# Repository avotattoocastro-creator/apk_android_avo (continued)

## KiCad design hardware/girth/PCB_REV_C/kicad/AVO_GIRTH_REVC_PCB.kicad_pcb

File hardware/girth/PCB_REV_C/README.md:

# AVO GIRTH · PCB de la cincha REV C (ECG) — 15/11/2026

PCB propia y compacta de la cincha, como la del casco V5: sustituye al XIAO ESP32-C6, al módulo GY-BNO08X y al
módulo CJMCU-30003 por los mismos chips soldados en una sola placa.

**Estado:** ver `out/AVO_GIRTH_REVC_PCB_REPORTE.md` (puerta superada) o `out/AVO_GIRTH_REVC_PCB_DIAGNOSTICO_REPORTE.md`.
**No fabricada. No verificada en hardware.**

## Placa
- **40 × 26 mm**, esquinas R2, 4 capas, **1,0 mm**, ENIG. 4 taladros Ø2,2 (tornillos M2 a la tapa) en (±17,8, ±10,8).
- **Todos los componentes en la cara F** (hacia la tapa, altura máx. 2,6 mm). La cara B apoya sobre la batería.
- In1 = GND macizo · F, In2 y B = señales · rellenos GND en F y B, +3V3 en In2.
- Arquitectura y GPIO: `DOCS/INFORME_PCB_REV_C.md`.

## Bloques
- **ESP32-C6-MINI-1U-N4** (13,2 × 12,5), antena FPC en el U.FL hacia el canto +X. Mismos GPIO que el XIAO: el
  firmware **AVO GIRTH 0.5.0** funciona sin cambios.
- **BNO085** soldado, por I²C (0x4A), cristal de 32,768 kHz, en el centro de la placa.
- **MAX30003** con 1,8 V propio (RT9080-18), oscilador MEMS SiT1533 en FCLK, filtros de entrada en los electrodos.
- **Cargador BQ24072** (247 mA para la LP403048 de 500 mAh), PTC en la batería y en el contacto de 5 V, 3,3 V RT9080-33.
- **Pogos por hilos** (pads pasantes): carga P1 5V · P2 GND · P3 DET; electrodos P4 ECG + · P5 REF · P6 ECG −;
  batería J2 + · J6 −.
- **Programación:** pads TP4 (D−), TP5 (D+), TP8 (5 V), TP3 (GND), TP2 (BOOT), TP1 (EN): USB nativo del C6 con una
  pinza de pogo-pins, la primera vez. Después, por radio.

## Fuente
`fuente/avo_girth_revc_pcb.py` (piezas y redes) → `fuente/place_revc.py` (colocación) → `fuente/build.py` (placa de
colocación + esquema) → CI `build-girth-pcb-revc.yml` (Freerouting, DRC/ERC, puerta, ficheros JLCPCB). Las huellas del
MAX30003 y del SiT1533 salen de EasyEDA/LCSC (`easyeda-fp-girth-revc.yml`); la del BNO085 coincide con la de EasyEDA.

## Pendiente antes de pedir
- **MAX30003CTI+** y **BNO085** sin existencias en JLCPCB el 15/11/2026: Global Sourcing o piezas enviadas.
- Código JLCPCB del ESP32-C6-MINI-1U-N4 (el C7558096 de la REV A sale sin existencias): ver `out_stock`.
- Cápsula REV 6 (más pequeña) en FreeCAD alrededor de esta placa y de la LP403048.

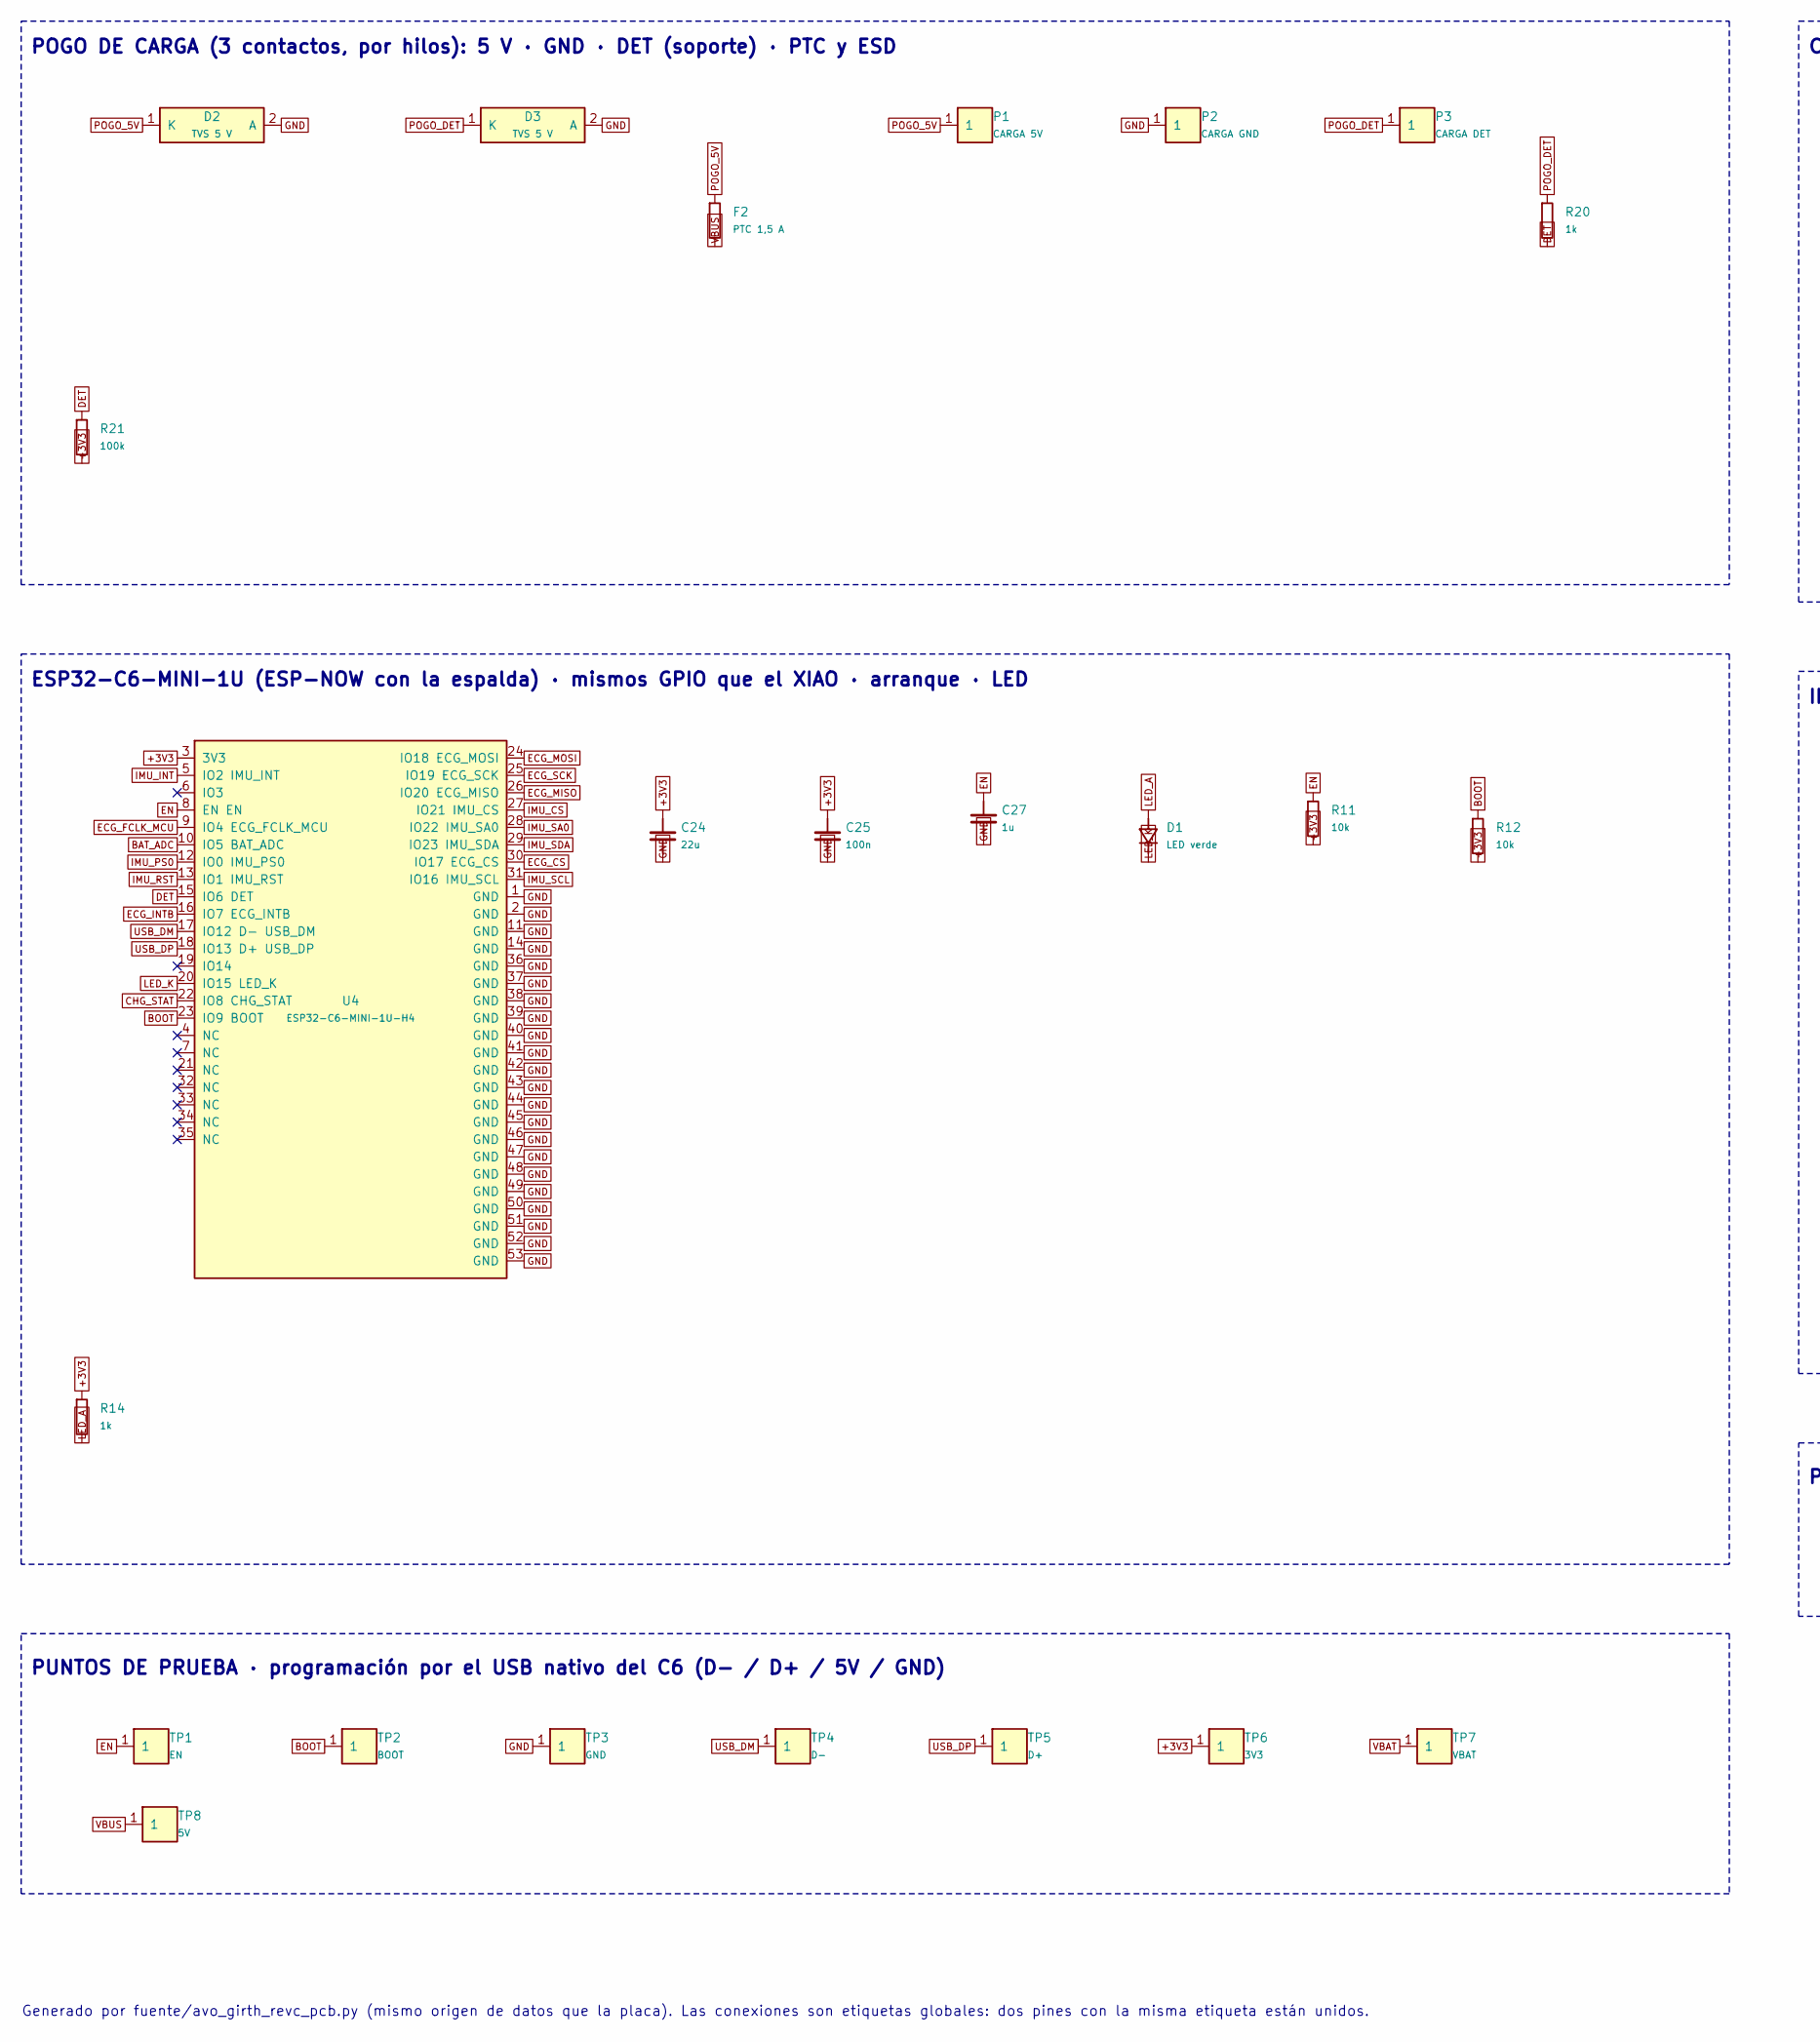
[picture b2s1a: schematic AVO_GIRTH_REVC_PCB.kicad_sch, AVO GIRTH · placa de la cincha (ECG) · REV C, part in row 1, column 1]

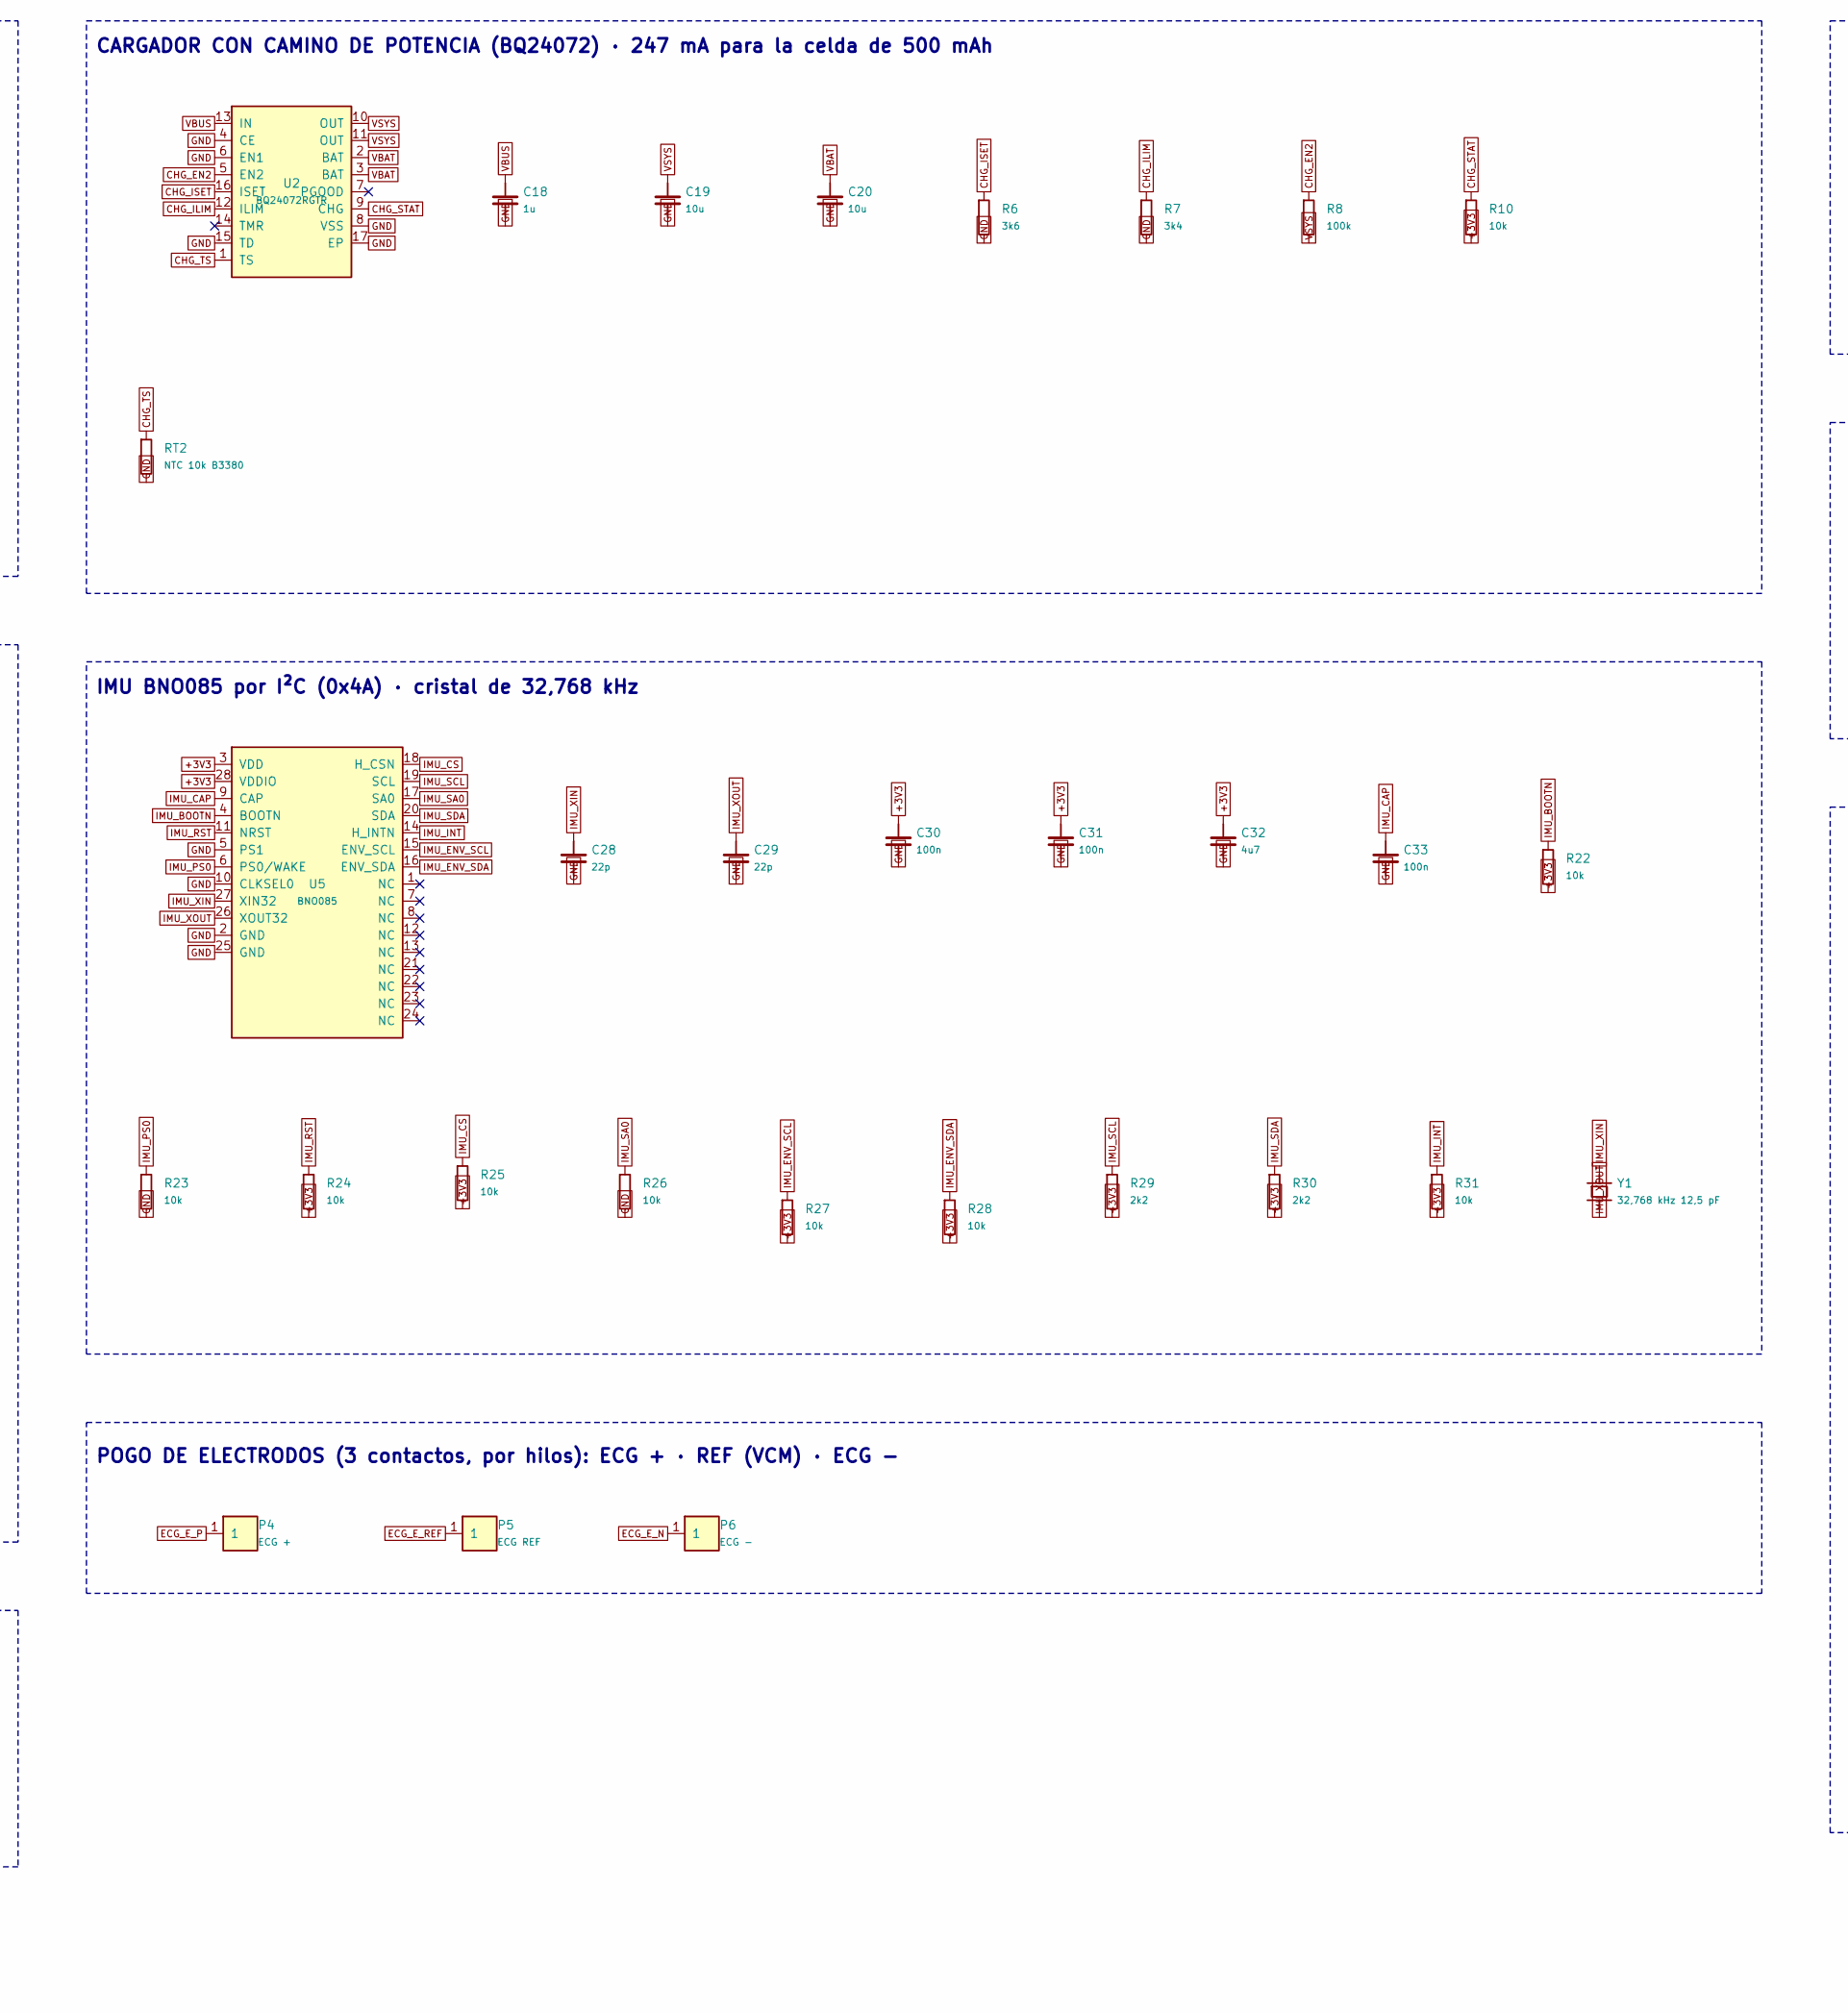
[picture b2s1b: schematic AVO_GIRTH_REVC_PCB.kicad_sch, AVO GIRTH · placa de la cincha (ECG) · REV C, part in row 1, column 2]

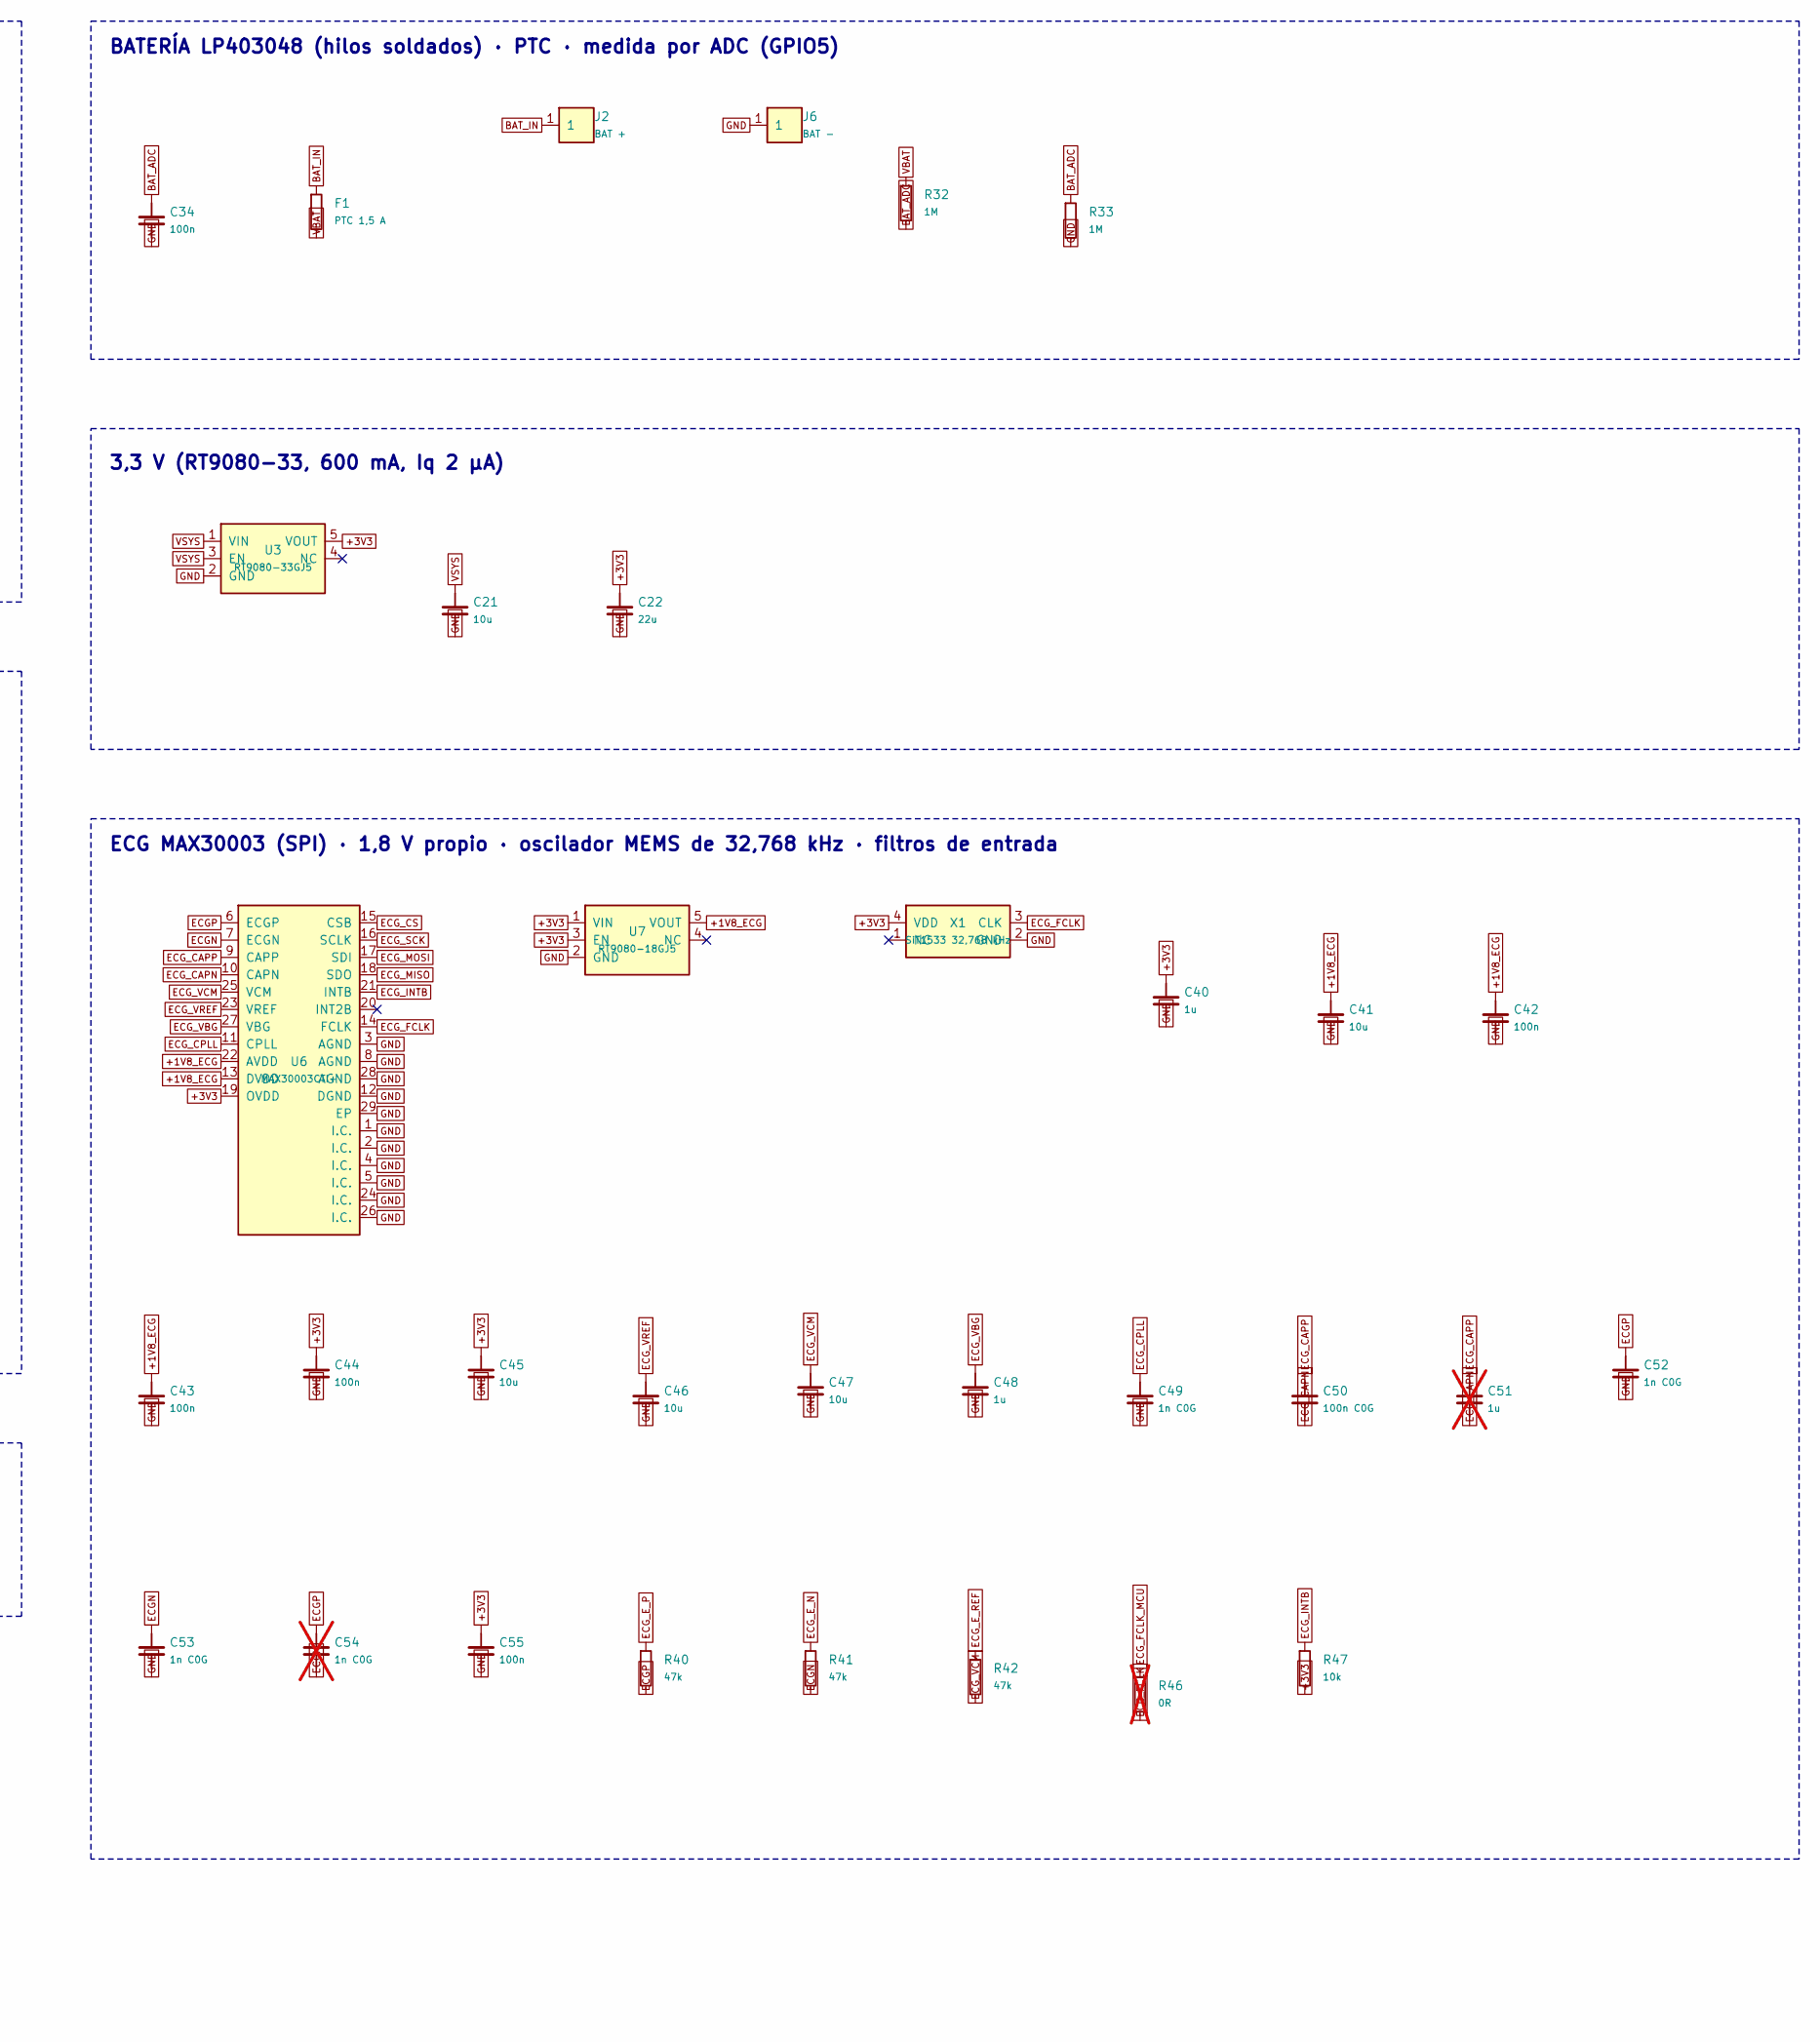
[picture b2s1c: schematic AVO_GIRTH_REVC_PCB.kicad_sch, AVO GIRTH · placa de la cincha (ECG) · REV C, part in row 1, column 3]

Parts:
C18, C27, C40, C48: 1u; C_0402_1005Metric; LCSC C52923
C19, C20, C21, C41, C45, C46, C47: 10u; C_0603_1608Metric; LCSC C96446
C22, C24: 22u; C_0805_2012Metric; LCSC C45783
C25, C30, C31, C33, C34, C42, C43, C44, C55: 100n; C_0402_1005Metric; LCSC C1525
C28, C29: 22p; C_0402_1005Metric; LCSC C1555
C32: 4u7; C_0603_1608Metric; LCSC C19666
C49, C52, C53: 1n C0G; C_0402_1005Metric; LCSC C53547
C50: 100n C0G; C_1206_3216Metric; LCSC C97946
C51: 1u; C_0402_1005Metric; LCSC C52923; not fitted
C54: 1n C0G; C_0402_1005Metric; LCSC C53547; not fitted
D1: LED verde; LED_0603_1608Metric; LCSC C2286
D2, D3: TVS 5 V; D_SOD-323; MPN PESD5V0S1BA; LCSC C2827694
F1, F2: PTC 1,5 A; Fuse_1206_3216Metric; MPN SMD1206P150TF; LCSC C20802
J2: BAT +; WirePad_D1.5_Drill0.8
J6: BAT -; WirePad_D1.5_Drill0.8
P1: CARGA 5V; WirePad_D1.5_Drill0.8
P2: CARGA GND; WirePad_D1.5_Drill0.8
P3: CARGA DET; WirePad_D1.5_Drill0.8
P4: ECG +; WirePad_D1.5_Drill0.8
P5: ECG REF; WirePad_D1.5_Drill0.8
P6: ECG -; WirePad_D1.5_Drill0.8
R6: 3k6; R_0402_1005Metric; LCSC C25891
R7: 3k4; R_0402_1005Metric; LCSC C4940
R8, R21: 100k; R_0402_1005Metric; LCSC C25741
R10, R11, R12, R22, R23, R24, R25, R26, R27, R28, R31, R47: 10k; R_0402_1005Metric; LCSC C25744
R14, R20: 1k; R_0402_1005Metric; LCSC C11702
R29, R30: 2k2; R_0402_1005Metric; LCSC C25879
R32, R33: 1M; R_0402_1005Metric; LCSC C26083
R40, R41, R42: 47k; R_0402_1005Metric; LCSC C25792
R46: 0R; R_0402_1005Metric; LCSC C17168; not fitted
RT2: NTC 10k B3380; R_0402_1005Metric; MPN NCP15XH103F03RC; LCSC C77131
TP1: EN; TestPoint_Pad_D1.0mm
TP2: BOOT; TestPoint_Pad_D1.0mm
TP3: GND; TestPoint_Pad_D1.0mm
TP4: D-; TestPoint_Pad_D1.0mm
TP5: D+; TestPoint_Pad_D1.0mm
TP6: 3V3; TestPoint_Pad_D1.0mm
TP7: VBAT; TestPoint_Pad_D1.0mm
TP8: 5V; TestPoint_Pad_D1.0mm
U2: BQ24072RGTR; VQFN-16-1EP_3x3mm_P0.5mm_EP1.68x1.68mm_ThermalVias; MPN BQ24072RGTR; LCSC C140288
U3: RT9080-33GJ5; SOT-23-5; MPN RT9080-33GJ5; LCSC C841192
U4: ESP32-C6-MINI-1U-H4; ESP32-C6-MINI-1U; MPN ESP32-C6-MINI-1U-H4 (alt. -N4); LCSC C20627095
U5: BNO085; CEVA_BNO08x_LGA-28_5.2x3.8mm_P0.5mm; MPN BNO085 (alt. BNO086); LCSC C5189642
U6: MAX30003CTI+; AVO_TQFN-28-1EP_5x5mm_P0.5mm_EP3.35mm; MPN MAX30003CTI+ (Analog Devices); LCSC C1519515
U7: RT9080-18GJ5; SOT-23-5; MPN RT9080-18GJ5; LCSC C426476
X1: SiT1533 32,768 kHz; AVO_SiT1533_2.0x1.2mm; MPN SIT1533AI-H4-DCC-32.768E (SiTime); LCSC C367058
Y1: 32,768 kHz 12,5 pF; Crystal_SMD_3215-2Pin_3.2x1.5mm; MPN Q13FC13500004; LCSC C32346

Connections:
+1V8_ECG: C41.1, C42.1, C43.1, U6.13 (DVDD), U6.22 (AVDD), U7.5 (VOUT)
+3V3: C22.1, C24.1, C25.1, C30.1, C31.1, C32.1, C40.1, C44.1, C45.1, C55.1, R10.2, R11.2, R12.2, R14.1, R21.2, R22.2, R24.2, R25.2, R27.2, R28.2, R29.2, R30.2, R31.2, R47.2, TP6.1, U3.5 (VOUT), U4.3 (3V3), U5.3 (VDD), U5.28 (VDDIO), U6.19 (OVDD), U7.1 (VIN), U7.3 (EN), X1.4 (VDD)
BAT_ADC: C34.1, R32.2, R33.1, U4.10 (IO5 BAT_ADC)
BAT_IN: F1.1, J2.1
BOOT: R12.1, TP2.1, U4.23 (IO9 BOOT)
CHG_EN2: R8.1, U2.5 (EN2)
CHG_ILIM: R7.1, U2.12 (ILIM)
CHG_ISET: R6.1, U2.16 (ISET)
CHG_STAT: R10.1, U2.9 (CHG), U4.22 (IO8 CHG_STAT)
CHG_TS: RT2.1, U2.1 (TS)
DET: R20.2, R21.1, U4.15 (IO6 DET)
ECGN: C53.1, C54.2, R41.2, U6.7 (ECGN)
ECGP: C52.1, C54.1, R40.2, U6.6 (ECGP)
ECG_CAPN: C50.2, C51.2, U6.10 (CAPN)
ECG_CAPP: C50.1, C51.1, U6.9 (CAPP)
ECG_CPLL: C49.1, U6.11 (CPLL)
ECG_CS: U4.30 (IO17 ECG_CS), U6.15 (CSB)
ECG_E_N: P6.1, R41.1
ECG_E_P: P4.1, R40.1
ECG_E_REF: P5.1, R42.1
ECG_FCLK: R46.2, U6.14 (FCLK), X1.3 (CLK)
ECG_FCLK_MCU: R46.1, U4.9 (IO4 ECG_FCLK_MCU)
ECG_INTB: R47.1, U4.16 (IO7 ECG_INTB), U6.21 (INTB)
ECG_MISO: U4.26 (IO20 ECG_MISO), U6.18 (SDO)
ECG_MOSI: U4.24 (IO18 ECG_MOSI), U6.17 (SDI)
ECG_SCK: U4.25 (IO19 ECG_SCK), U6.16 (SCLK)
ECG_VBG: C48.1, U6.27 (VBG)
ECG_VCM: C47.1, R42.2, U6.25 (VCM)
ECG_VREF: C46.1, U6.23 (VREF)
EN: C27.1, R11.1, TP1.1, U4.8 (EN EN)
GND: C18.2, C19.2, C20.2, C21.2, C22.2, C24.2, C25.2, C27.2, C28.2, C29.2, C30.2, C31.2, C32.2, C33.2, C34.2, C40.2, C41.2, C42.2, C43.2, C44.2, C45.2, C46.2, C47.2, C48.2, C49.2, C52.2, C53.2, C55.2, D2.2 (A), D3.2 (A), J6.1, P2.1, R6.2, R7.2, R23.2, R26.2, R33.2, RT2.2, TP3.1, U2.4 (CE), U2.6 (EN1), U2.8 (VSS), U2.15 (TD), U2.17 (EP), U3.2 (GND), U4.1 (GND), U4.2 (GND), U4.11 (GND), U4.14 (GND), U4.36 (GND), U4.37 (GND), U4.38 (GND), U4.39 (GND), U4.40 (GND), U4.41 (GND), U4.42 (GND), U4.43 (GND), U4.44 (GND), U4.45 (GND), U4.46 (GND), U4.47 (GND), U4.48 (GND), U4.49 (GND), U4.50 (GND), U4.51 (GND), U4.52 (GND), U4.53 (GND), U5.2 (GND), U5.5 (PS1), U5.10 (CLKSEL0), U5.25 (GND), U6.1 (I.C.), U6.2 (I.C.), U6.3 (AGND), U6.4 (I.C.), U6.5 (I.C.), U6.8 (AGND), U6.12 (DGND), U6.24 (I.C.), U6.26 (I.C.), U6.28 (AGND), U6.29 (EP), U7.2 (GND), X1.2 (GND)
IMU_BOOTN: R22.1, U5.4 (BOOTN)
IMU_CAP: C33.1, U5.9 (CAP)
IMU_CS: R25.1, U4.27 (IO21 IMU_CS), U5.18 (H_CSN)
IMU_ENV_SCL: R27.1, U5.15 (ENV_SCL)
IMU_ENV_SDA: R28.1, U5.16 (ENV_SDA)
IMU_INT: R31.1, U4.5 (IO2 IMU_INT), U5.14 (H_INTN)
IMU_PS0: R23.1, U4.12 (IO0 IMU_PS0), U5.6 (PS0/WAKE)
IMU_RST: R24.1, U4.13 (IO1 IMU_RST), U5.11 (NRST)
IMU_SA0: R26.1, U4.28 (IO22 IMU_SA0), U5.17 (SA0)
IMU_SCL: R29.1, U4.31 (IO16 IMU_SCL), U5.19 (SCL)
IMU_SDA: R30.1, U4.29 (IO23 IMU_SDA), U5.20 (SDA)
IMU_XIN: C28.1, U5.27 (XIN32), Y1.1
IMU_XOUT: C29.1, U5.26 (XOUT32), Y1.2
LED_A: D1.2 (A), R14.2
LED_K: D1.1 (K), U4.20 (IO15 LED_K)
POGO_5V: D2.1 (K), F2.1, P1.1
POGO_DET: D3.1 (K), P3.1, R20.1
USB_DM: TP4.1, U4.17 (IO12 D- USB_DM)
USB_DP: TP5.1, U4.18 (IO13 D+ USB_DP)
VBAT: C20.1, F1.2, R32.1, TP7.1, U2.2 (BAT), U2.3 (BAT)
VBUS: C18.1, F2.2, TP8.1, U2.13 (IN)
VSYS: C19.1, C21.1, R8.2, U2.10 (OUT), U2.11 (OUT), U3.1 (VIN), U3.3 (EN)

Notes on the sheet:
POGO DE CARGA (3 contactos, por hilos): 5 V · GND · DET (soporte) · PTC y ESD
CARGADOR CON CAMINO DE POTENCIA (BQ24072) · 247 mA para la celda de 500 mAh
3,3 V (RT9080-33, 600 mA, Iq 2 µA)
ESP32-C6-MINI-1U (ESP-NOW con la espalda) · mismos GPIO que el XIAO · arranque · LED
IMU BNO085 por I²C (0x4A) · cristal de 32,768 kHz
ECG MAX30003 (SPI) · 1,8 V propio · oscilador MEMS de 32,768 kHz · filtros de entrada
BATERÍA LP403048 (hilos soldados) · PTC · medida por ADC (GPIO5)
POGO DE ELECTRODOS (3 contactos, por hilos): ECG + · REF (VCM) · ECG −
PUNTOS DE PRUEBA · programación por el USB nativo del C6 (D− / D+ / 5V / GND)
Generado por fuente/avo_girth_revc_pcb.py (mismo origen de datos que la placa). Las conexiones son etiquetas globales: dos pines con la misma etiqueta están unidos.

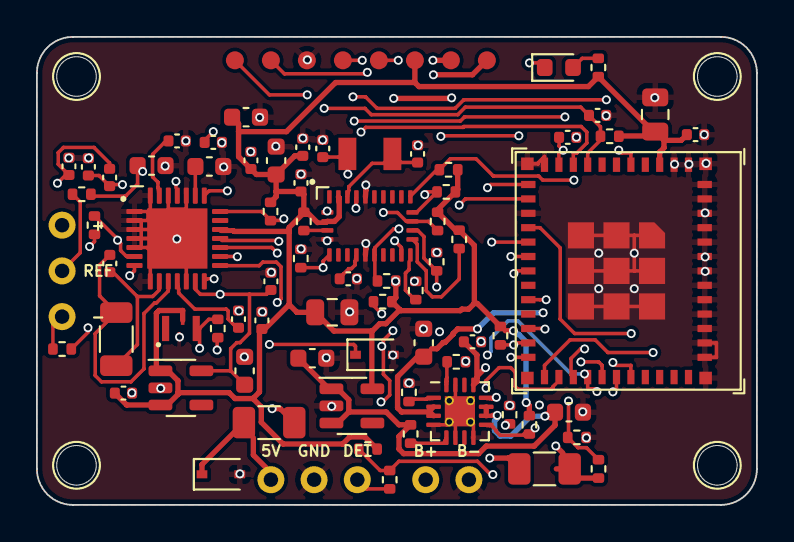
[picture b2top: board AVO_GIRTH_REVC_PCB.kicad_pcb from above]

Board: 4 copper layers, 40.0 x 26.0 mm, 91 parts (0 on the bottom side), 53 nets.

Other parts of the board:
H1, H2, H3, H4: TALADRO M2; AVO_Taladro_NPTH_D2.2

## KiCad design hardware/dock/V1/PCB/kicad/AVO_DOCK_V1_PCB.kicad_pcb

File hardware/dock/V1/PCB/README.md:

# AVO DOCK V1 · PCB REV A (15/11/2026)

**Estado:** diseño verificado por software en el CI con KiCad 9 (ejecución 43789462892):
- DRC: 0 errores y 0 conexiones incompletas;
- paridad esquema ↔ placa: 0;
- ERC: 0/0;
- puerta superada.

Los ficheros de fabricación están en `out/FINAL/`. **No fabricada. No verificada en hardware.**

**Ruteado:** Freerouting 1.9.0 de la ejecución 43788505774. Se guarda tal cual en `kicad/AVO_DOCK_V1_PCB_ruteado.kicad_pcb` y el CI lo reutiliza sin volver a rutear. Si cambia la colocación, hay que borrar ese fichero.

## Cómo se genera
```
cd fuente
python3 place_dock.py      # colocación → colocacion_dock.json y ../pcb_mecanica.json (lo lee el CAD)
python3 build.py           # placa de colocación + vías a planos, esquema, proyecto y piezas.json
```
En el CI se hace el ruteado (Freerouting 1.9.0), el relleno de zonas, el DRC con paridad y el ERC. Después viene la puerta de fabricación (`fuente/gate.py`). Solo si la supera se generan los Gerber, la BOM y el CPL de JLCPCB y el STEP en `out/FINAL/`.

## Placa
- 130 × 76 mm, esquinas R3, 4 capas, 1,6 mm, ENIG. Todos los componentes en la cara F.
- Capas: F.Cu y B.Cu de señal (con relleno GND tras el ruteado); In1 = plano GND; In2 = plano +3V3 (vía desde cada pad).
- **Zona de red** en (−65…−46, −12…38) con un **foso de 6,5 mm** sin cobre en ninguna capa. Las pistas de red (1,0 mm, F.Cu) las traza el generador.
- 4 taladros NPTH Ø3,2 para M3 de nailon.

Arquitectura, conexiones y pendientes: `../DOCS/ARQUITECTURA.md`.

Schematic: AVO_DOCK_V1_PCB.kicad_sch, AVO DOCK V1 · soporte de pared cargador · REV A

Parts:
C1, C5: 47u 6V3; C_0805_2012Metric; LCSC C16780
C2, C8, C10, C13, C14, C16, C20, C21, C22, C23, C24, C25, C27, C28, C29, C40, C41, C42, C43, C44, C45, C46, C47: 100n; C_0402_1005Metric; LCSC C1525
C3, C15, C48, C49, C50, C51: 10u 25V; C_0603_1608Metric; LCSC C96446
C4: 100u 10V; CP_EIA-3528-21_Kemet-B; MPN TAJB107K010RNJ (AVX) o equivalente
C6, C7, C9: 22u 10V; C_0805_2012Metric; LCSC C45783
C11, C12: 1u; C_0402_1005Metric; LCSC C52923
C26: 4u7; C_0603_1608Metric; LCSC C19666
C30, C31: 18p; C_0402_1005Metric; LCSC C1549
D1, D10, D11, D12, D13, D14, D15, D16, D17: TVS 5 V; D_SOD-323; MPN PESD5V0S1BA; LCSC C2827694
F1: T1A 250V; Fuse_Littelfuse_372_D8.50mm; MPN Littelfuse 37211000411 (TR5, T 1 A)
F2: PTC 1,5 A; Fuse_1206_3216Metric; MPN SMD1206P150TF; LCSC C20802
J1: RED L; WirePad_D2.6_Drill1.3
J2: RED N; WirePad_D2.6_Drill1.3
J3: USB-C PC; USB_C_Receptacle_HRO_TYPE-C-31-M-12; MPN TYPE-C-31-M-12 (HRO); LCSC C165948
J4: PANTALLA 2" ST7789; JST_GH_SM08B-GHS-TB_1x08-1MP_P1.25mm_Horizontal; MPN SM08B-GHS-TB (JST)
P1: A VBUS; WirePad_D1.7_Drill0.9
P2: A D-; WirePad_D1.7_Drill0.9
P3: A D+; WirePad_D1.7_Drill0.9
P4: A GND; WirePad_D1.7_Drill0.9
P5: A AUX; WirePad_D1.7_Drill0.9
P6: B VBUS; WirePad_D1.7_Drill0.9
P7: B D-; WirePad_D1.7_Drill0.9
P8: B D+; WirePad_D1.7_Drill0.9
P9: B GND; WirePad_D1.7_Drill0.9
P10: B AUX; WirePad_D1.7_Drill0.9
P11: GA +5V; WirePad_D1.7_Drill0.9
P12: GA GND; WirePad_D1.7_Drill0.9
P13: GA MTCK; WirePad_D1.7_Drill0.9
P14: GB +5V; WirePad_D1.7_Drill0.9
P15: GB GND; WirePad_D1.7_Drill0.9
P16: GB MTCK; WirePad_D1.7_Drill0.9
P20: PULSADOR; WirePad_D1.7_Drill0.9
P21: PULSADOR GND; WirePad_D1.7_Drill0.9
PS1: IRM-20-5; Converter_ACDC_MeanWell_IRM-20-xx_THT; MPN Mean Well IRM-20-5 (5 V 4 A)
Q1, Q1B, Q2: AO3401A; SOT-23; LCSC C15127
Q3: 2N7002; SOT-23; LCSC C8545
R1, R2, R5, R6, R8, R9, R10, R12, R13, R17, R28, R44, R45, R46, R47: 100k; R_0402_1005Metric; LCSC C25741
R3, R4: 5k1; R_0402_1005Metric; LCSC C25905
R7, R14, R21, R22, R23, R24, R26, R29, R30, R31, R32: 10k; R_0402_1005Metric; LCSC C25744
R11: 0R; R_0402_1005Metric; LCSC C17168
R15, R16, R52, R53, R54, R55: 22R; R_0402_1005Metric; LCSC C25092
R20: 12k; R_0402_1005Metric; LCSC C25752
R27: 68k; R_0402_1005Metric; LCSC C36871
R40, R41: 24k9; R_0402_1005Metric
R42, R43: 49k9; R_0402_1005Metric
R48, R49, R50, R51: 50m 1%; R_0805_2012Metric
R56, R57, R60, R61: 1k; R_0402_1005Metric; LCSC C11702
R62, R63: 47k; R_0402_1005Metric; LCSC C25792
RV1: MOV 275 VAC; RV_Disc_D7mm_W4.8mm_P5mm; MPN S07K275 (TDK) o equivalente
TP1: EN; TestPoint_Pad_D1.0mm
TP2: BOOT; TestPoint_Pad_D1.0mm
TP3: GND; TestPoint_Pad_D1.0mm
TP4: TXD0; TestPoint_Pad_D1.0mm
TP5: RXD0; TestPoint_Pad_D1.0mm
TP6: 3V3; TestPoint_Pad_D1.0mm
TP7: 5V_SYS; TestPoint_Pad_D1.0mm
TP8: 5V_RED; TestPoint_Pad_D1.0mm
TP9: VBUS_PC; TestPoint_Pad_D1.0mm
U1, U18, U19: USBLC6-2SC6; SOT-23-6; LCSC C7519
U2: AMS1117-3.3; SOT-223; MPN AMS1117-3.3; LCSC C6186
U3: ESP32-S3-MINI-1U-N8; ESP32-S3-MINI-1U; MPN ESP32-S3-MINI-1U-N8; LCSC C2980299
U4, U5: TS3USB221; DFN-10-1EP_3x3mm_P0.5mm_EP1.65x2.38mm; MPN TS3USB221ADRCR
U6: USB2514B-I/M2; QFN-36-1EP_6x6mm_P0.5mm_EP3.7x3.7mm_ThermalVias; MPN USB2514B-I/M2 (Microchip); LCSC C220679
U10, U11, U12, U13: TPS2553DBVR; SOT-23-6; MPN TPS2553DBVR (TI)
U14, U15, U16, U17: INA180A2; SOT-23-5; MPN INA180A2IDBVR (TI)
Y1: 24 MHz; Crystal_SMD_3225-4Pin_3.2x2.5mm; MPN X322524MOB4SI (Yangxing) 24 MHz 12 pF o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

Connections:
+3V3: C7.1, C8.1, C9.1, C10.1, C11.1, C13.1, C14.1, C15.1, C20.1, C21.1, C22.1, C23.1, C24.1, C25.1, C26.1, C44.1, C45.1, C46.1, C47.1, J4.2 (VCC), R14.2, R24.2, R26.2, R30.2, R31.2, R32.2, R62.2, R63.2, TP6.1, U2.2 (VOUT), U2.4 (TAB), U3.3 (3V3), U4.10 (VCC), U5.10 (VCC), U6.5 (VDDA33), U6.8 (DN4_DM/PRT_DIS_M4), U6.9 (DN4_DP/PRT_DIS_P4), U6.10 (VDDA33), U6.13 (OCS_N1), U6.15 (VDD33), U6.17 (OCS_N2), U6.19 (OCS_N3), U6.21 (OCS_N4), U6.23 (VDD33), U6.29 (VDDA33), U6.36 (VDDA33), U14.5 (VS), U15.5 (VS), U16.5 (VS), U17.5 (VS)
+5V_RED: C1.1, C2.1, PS1.4 (+V), Q1.3 (D), Q1B.3 (D), R1.1, R7.1, R11.1, TP8.1
+5V_SYS: C4.1 (+), C5.1, C6.1, C40.1, C41.1, C42.1, C43.1, Q1.2 (S), Q1B.2 (S), Q2.2 (S), R8.2, R12.1, TP7.1, U2.3 (VIN), U10.1 (IN), U11.1 (IN), U12.1 (IN), U13.1 (IN)
ACG: Q1.1 (G), Q1B.1 (G), Q3.3 (D), R8.1
ACOK_SNS: R1.2, R2.1, U3.14 (IO10 ACOK_SNS)
AC_L: F1.2, PS1.1 (AC/L), RV1.1
AC_L_IN: F1.1, J1.1
AC_N: J2.1, PS1.2 (AC/N), RV1.2
AUX_A: R56.1, U3.36 (IO40 AUX_A)
AUX_B: R57.1, U3.37 (IO41 AUX_B)
AUX_CA_P: D14.1 (K), P5.1, R56.2
AUX_CB_P: D15.1 (K), P10.1, R57.2
BOOT: TP2.1, U3.4 (IO0 BOOT)
BTN: C16.1, P20.1, R32.1, U3.30 (IO48 BTN)
CA_DM: R53.1, U6.1 (DN1_DM)
CA_DM_P: P2.1, R53.2, U18.3 (IO2), U18.4 (IO2)
CA_DP: R52.1, U6.2 (DN1_DP)
CA_DP_P: P3.1, R52.2, U18.1 (IO1), U18.6 (IO1)
CB_DM: R55.1, U6.3 (DN2_DM)
CB_DM_P: P7.1, R55.2, U19.3 (IO2), U19.4 (IO2)
CB_DP: R54.1, U6.4 (DN2_DP)
CB_DP_P: P8.1, R54.2, U19.1 (IO1), U19.6 (IO1)
CC1: J3.A5 (CC1), R3.1, U3.12 (IO8 CC1)
CC2: J3.B5 (CC2), R4.1, U3.13 (IO9 CC2)
EN: C12.1, R14.1, TP1.1, U3.45 (EN EN)
EN_CA: R44.1, U3.21 (IO17 EN_CA), U10.3 (EN)
EN_CB: R45.1, U3.22 (IO18 EN_CB), U11.3 (EN)
EN_GA: R46.1, U3.25 (IO21 EN_GA), U12.3 (EN)
EN_GB: R47.1, U3.27 (IO47 EN_GB), U13.3 (EN)
FLT_C: R30.1, U3.28 (IO33 FLT_C), U10.4 (FAULT), U11.4 (FAULT)
FLT_G: R31.1, U3.29 (IO34 FLT_G), U12.4 (FAULT), U13.4 (FAULT)
GA_IO_P: D16.1 (K), P13.1, R60.2
GB_IO_P: D17.1 (K), P16.1, R61.2
GIRTH_A_IO: R60.1, R62.1, U3.31 (IO35 GIRTH_A_IO)
GIRTH_B_IO: R61.1, R63.1, U3.32 (IO36 GIRTH_B_IO)
GND: C1.2, C2.2, C3.2, C4.2 (-), C5.2, C6.2, C7.2, C8.2, C9.2, C10.2, C11.2, C12.2, C13.2, C14.2, C15.2, C16.2, C20.2, C21.2, C22.2, C23.2, C24.2, C25.2, C26.2, C27.2, C28.2, C29.2, C30.2, C31.2, C40.2, C41.2, C42.2, C43.2, C44.2, C45.2, C46.2, C47.2, C48.2, C49.2, C50.2, C51.2, D1.2 (A), D10.2 (A), D11.2 (A), D12.2 (A), D13.2 (A), D14.2 (A), D15.2 (A), D16.2 (A), D17.2 (A), J3.A1 (GND), J3.A12 (GND), J3.B1 (GND), J3.B12 (GND), J3.S1 (SHIELD), J4.1 (GND), J4.MP, P4.1, P9.1, P12.1, P15.1, P21.1, PS1.3 (-V), Q3.2 (S), R2.2, R3.2, R4.2, R6.2, R9.2, R10.2, R13.2, R17.2, R20.2, R21.2, R22.2, R23.2, R28.2, R40.2, R41.2, R42.2, R43.2, R44.2, R45.2, R46.2, R47.2, TP3.1, U1.2 (GND), U2.1 (GND), U3.1 (GND), U3.2 (GND), U3.42 (GND), U3.43 (GND), U3.46 (GND), U3.47 (GND), U3.48 (GND), U3.49 (GND), U3.50 (GND), U3.51 (GND), U3.52 (GND), U3.53 (GND), U3.54 (GND), U3.55 (GND), U3.56 (GND), U3.57 (GND), U3.58 (GND), U3.59 (GND), U3.60 (GND), U3.61 (GND), U3.62 (GND), U3.63 (GND), U3.64 (GND), U3.65 (GND), U4.5 (GND), U4.6 (OE), U4.11 (EP), U5.5 (GND), U5.6 (OE), U5.11 (EP), U6.11 (TEST), U6.37 (VSS), U10.2 (GND), U11.2 (GND), U12.2 (GND), U13.2 (GND), U14.2 (GND), U15.2 (GND), U16.2 (GND), U17.2 (GND), U18.2 (GND), U19.2 (GND), Y1.2 (GND), Y1.4 (GND)
HUB_CFG0: R21.1, U6.24 (SCL/CFG_SEL0)
HUB_CFG1: R22.1, U6.25 (HS_IND/CFG_SEL1)
HUB_CRFILT: C27.1, U6.14 (CRFILT)
HUB_DN3_DM: U5.2 (1D-), U6.6 (DN3_DM)
HUB_DN3_DP: U5.1 (1D+), U6.7 (DN3_DP)
HUB_LOCALPWR: R24.1, U6.28 (SUSP_IND/LOCAL_PWR)
HUB_NONREM1: R23.1, U6.22 (SDA/NON_REM1)
HUB_PLLFILT: C28.1, U6.34 (PLLFILT)
HUB_RBIAS: R20.1, U6.35 (RBIAS)
HUB_RST_N: C29.1, R26.1, U3.33 (IO37 HUB_RST_N), U6.26 (RESET_N)
HUB_UP_DM: U4.7 (D-), U6.30 (USBDM_UP)
HUB_UP_DP: U4.8 (D+), U6.31 (USBDP_UP)
HUB_VBUS_DET: R27.2, R28.1, R29.2, U6.27 (VBUS_DET)
HUB_VBUS_EN: R29.1, U3.34 (IO38 HUB_VBUS_EN)
ILIM_CA: R40.1, U10.5 (ILIM)
ILIM_CB: R41.1, U11.5 (ILIM)
ILIM_GA: R42.1, U12.5 (ILIM)
ILIM_GB: R43.1, U13.5 (ILIM)
ISNS_CA: U3.5 (IO1 ISNS_CA), U14.1 (OUT)
ISNS_CB: U3.6 (IO2 ISNS_CB), U15.1 (OUT)
ISNS_GA: U3.8 (IO4 ISNS_GA), U16.1 (OUT)
ISNS_GB: U3.9 (IO5 ISNS_GB), U17.1 (OUT)
LCD_BL: J4.8 (BLK), U3.20 (IO16 LCD_BL)
LCD_CS: J4.7 (CS), U3.17 (IO13 LCD_CS)
LCD_DC: J4.6 (DC), U3.18 (IO14 LCD_DC)
LCD_MOSI: J4.4 (SDA), U3.15 (IO11 LCD_MOSI)
LCD_RST: J4.5 (RES), U3.19 (IO15 LCD_RST)
LCD_SCK: J4.3 (SCL), U3.16 (IO12 LCD_SCK)
RED_DET: Q3.1 (G), R7.2, R10.1
S3H_DM: U4.4 (2D-), U5.4 (2D-)
S3H_DP: U4.3 (2D+), U5.3 (2D+)
S3_DM: R16.1, U3.23 (IO19 D- S3_DM)
S3_DM_R: R16.2, U5.7 (D-)
S3_DP: R15.1, U3.24 (IO20 D+ S3_DP)
S3_DP_R: R15.2, U5.8 (D+)
U0RX: TP5.1, U3.40 (RXD0 U0RX)
U0TX: TP4.1, U3.39 (TXD0 U0TX)
USBC_DM_C: J3.A7 (D-), J3.B7 (D-), U1.3 (IO2), U1.4 (IO2), U4.2 (1D-)
USBC_DP_C: J3.A6 (D+), J3.B6 (D+), U1.1 (IO1), U1.6 (IO1), U4.1 (1D+)
USBG: Q2.1 (G), R9.1, R11.2
USB_SEL: R17.1, U3.35 (IO39 USB_SEL), U4.9 (S), U5.9 (S)
V5_SNS: R12.2, R13.1, U3.10 (IO6 V5_SNS)
VBUSC_SNS: R5.2, R6.1, U3.11 (IO7 VBUSC_SNS)
VBUS_C_RAW: D1.1 (K), F2.1, J3.A4 (VBUS), J3.A9 (VBUS), J3.B4 (VBUS), J3.B9 (VBUS)
VBUS_PC: C3.1, F2.2, Q2.3 (D), R5.1, R27.1, TP9.1, U1.5 (VBUS)
VPOGO_CA: C48.1, D10.1 (K), P1.1, R48.2, U14.4 (IN-), U18.5 (VBUS)
VPOGO_CB: C49.1, D11.1 (K), P6.1, R49.2, U15.4 (IN-), U19.5 (VBUS)
VPOGO_GA: C50.1, D12.1 (K), P11.1, R50.2, U16.4 (IN-)
VPOGO_GB: C51.1, D13.1 (K), P14.1, R51.2, U17.4 (IN-)
VSW_CA: R48.1, U10.6 (OUT), U14.3 (IN+)
VSW_CB: R49.1, U11.6 (OUT), U15.3 (IN+)
VSW_GA: R50.1, U12.6 (OUT), U16.3 (IN+)
VSW_GB: R51.1, U13.6 (OUT), U17.3 (IN+)
XTAL_I: C30.1, U6.33 (XTALIN), Y1.1
XTAL_O: C31.1, U6.32 (XTALOUT), Y1.3

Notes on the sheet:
SELECTOR DE ALIMENTACIÓN: prioridad a la red, sin retroalimentar el PC ni el IRM (PMOS)
USB-C DEL PC: Rd 5,1 k (consumidor) · PTC 1,5 A · ESD
CASCO A: TPS2553 (≈ 1 A) · shunt 50 mΩ + INA180A2 · pogo 5 contactos (VBUS · D− · D+ · GND · AUX)
CASCO B: TPS2553 (≈ 1 A) · shunt 50 mΩ + INA180A2 · pogo 5 contactos
CINCHA A: TPS2553 (≈ 0,5 A) · shunt 50 mΩ + INA180A2 · pogo 3 contactos (+5 V · GND · MTCK)
CINCHA B: TPS2553 (≈ 0,5 A) · shunt 50 mΩ + INA180A2 · pogo 3 contactos
PANTALLA IPS 2,0" ST7789 (JST-GH 8) · pulsador frontal
RED 230 V~ (ZONA AISLADA, FOSO 6,5 mm): fusible T1 A · varistor 275 V · Mean Well IRM-20-5 (5 V 4 A)
3,3 V (AMS1117-3.3)
ESP32-S3-MINI-1U-N8: BLE + Wi-Fi con la app · USB OTG · pantalla · puertos
CONMUTADORES USB TS3USB221: modo PC (USB_SEL = 0) / modo autónomo, S3 anfitrión (USB_SEL = 1)
HUB USB2514B: 1 = casco A · 2 = casco B · 3 = S3 · 4 desactivado · cristal 24 MHz
PUNTOS DE PRUEBA
Generado por fuente/avo_dock_v1_pcb.py (mismo origen de datos que la placa). Las conexiones son etiquetas globales: dos pines con la misma etiqueta están unidos.
